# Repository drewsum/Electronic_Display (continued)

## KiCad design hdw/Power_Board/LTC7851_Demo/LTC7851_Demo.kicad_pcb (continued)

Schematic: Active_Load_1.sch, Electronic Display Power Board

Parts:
C1101: 1uF; C_0603; Voltage 16V; Digi-Key PN 1276-6524-1-ND
C1102: 0.1uF; C_0603; Voltage 50V; Digi-Key PN 490-4779-1-ND
C1103: 10uF; CP_Tantalum_Case-B_EIA-3528-21_Reflow; Voltage 16V; Tolerance 10%; Digi-Key PN 399-5034-1-ND
J1101: FG_LOAD; Pin_Header_Straight_1x02_Pitch2.54mm
J1102: ISNS; Pin_Header_Straight_1x02_Pitch2.54mm
Q1101, Q1102: IPC100N04S51R7ATMA1; TDSON-8-1; Digi-Key PN BSC123N10LSGATMA1CT-ND
R1101, R1105, R1106: 10k; R_0603; Tolerance 1%; Digi-Key PN RHM10KADCT-ND
R1102, R1103, R1104: 10; R_0603; Tolerance 1%; Digi-Key PN YAG3351CT-ND
R1107, R1108: 5m; R_2512; Tolerance 1%; Digi-Key PN YAG2145CT-ND
U1101: LT1010DD; DFN-8-1EP_3x3mm_Pitch0.5mm; Digi-Key PN LT1010CDD#PBF-ND

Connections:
+5V: Q1101.5 (D), Q1102.5 (D); also elsewhere on the board
+12V: C1101.1, C1102.1, C1103.1, R1102.1, U1101.1 (V+); also elsewhere on the board
GND: C1101.2, C1102.2, C1103.2, J1101.2, J1102.2, R1101.2, R1105.2, R1106.2, R1107.2, R1108.2, U1101.6 (V-), U1101.9 (V-); also elsewhere on the board
LOAD_GATE: R1103.2, R1104.2, U1101.3; also elsewhere on the board
unnamed: J1101.1, R1101.1, U1101.8
unnamed: J1102.1, Q1101.1 (S), Q1101.2 (S), Q1101.3 (S), R1107.1
unnamed: Q1101.4 (G), R1103.1, R1105.1
unnamed: Q1102.1 (S), Q1102.2 (S), Q1102.3 (S), R1108.1
unnamed: Q1102.4 (G), R1104.1, R1106.1
unnamed: R1102.2, U1101.2 (Bias)

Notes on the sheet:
11. Active Load Driver and Active Load Bank 1

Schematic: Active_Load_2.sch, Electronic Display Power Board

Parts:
Q1201, Q1202: IPC100N04S51R7ATMA1; TDSON-8-1; Digi-Key PN BSC123N10LSGATMA1CT-ND
R1201, R1202: 10; R_0603; Tolerance 1%; Digi-Key PN YAG3351CT-ND
R1203, R1204: 10k; R_0603; Tolerance 1%; Digi-Key PN RHM10KADCT-ND
R1205, R1206: 5m; R_2512; Tolerance 1%; Digi-Key PN YAG2145CT-ND

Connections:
+5V: Q1201.5 (D), Q1202.5 (D); also elsewhere on the board
GND: R1203.2, R1204.2, R1205.2, R1206.2; also elsewhere on the board
LOAD_GATE: R1201.2, R1202.2; also elsewhere on the board
unnamed: Q1201.1 (S), Q1201.2 (S), Q1201.3 (S), R1205.1
unnamed: Q1201.4 (G), R1201.1, R1203.1
unnamed: Q1202.1 (S), Q1202.2 (S), Q1202.3 (S), R1206.1
unnamed: Q1202.4 (G), R1202.1, R1204.1

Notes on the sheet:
12. Active Load Bank 2

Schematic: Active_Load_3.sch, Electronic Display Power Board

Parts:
Q1301, Q1302: IPC100N04S51R7ATMA1; TDSON-8-1; Digi-Key PN BSC123N10LSGATMA1CT-ND
R1301, R1302: 10; R_0603; Tolerance 1%; Digi-Key PN YAG3351CT-ND
R1303, R1304: 10k; R_0603; Tolerance 1%; Digi-Key PN RHM10KADCT-ND
R1305, R1306: 5m; R_2512; Tolerance 1%; Digi-Key PN YAG2145CT-ND

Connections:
+5V: Q1301.5 (D), Q1302.5 (D); also elsewhere on the board
GND: R1303.2, R1304.2, R1305.2, R1306.2; also elsewhere on the board
LOAD_GATE: R1301.2, R1302.2; also elsewhere on the board
unnamed: Q1301.1 (S), Q1301.2 (S), Q1301.3 (S), R1305.1
unnamed: Q1301.4 (G), R1301.1, R1303.1
unnamed: Q1302.1 (S), Q1302.2 (S), Q1302.3 (S), R1306.1
unnamed: Q1302.4 (G), R1302.1, R1304.1

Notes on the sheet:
13. Active Load Bank 3

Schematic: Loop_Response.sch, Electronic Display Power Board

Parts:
J1401: VOUT; Pin_Header_Straight_1x02_Pitch2.54mm
J1402: LOOP_TAP; Pin_Header_Straight_1x02_Pitch2.54mm
J1403: Wave_Gen_In; Pin_Header_Straight_1x02_Pitch2.54mm
T1401: 1:1 Pulse Transformer; Murata_78601_9C; Digi-Key PN 811-2650-ND

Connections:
+5V: J1401.1, T1401.4 (SB); also elsewhere on the board
GND: J1401.2, J1402.2, J1403.2, T1401.2 (AB); also elsewhere on the board
LOOP_TAP: J1402.1, T1401.3 (SA); also elsewhere on the board
unnamed: J1403.1, T1401.1 (AA)

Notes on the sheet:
14. Open Loop Transfer Function Test Components

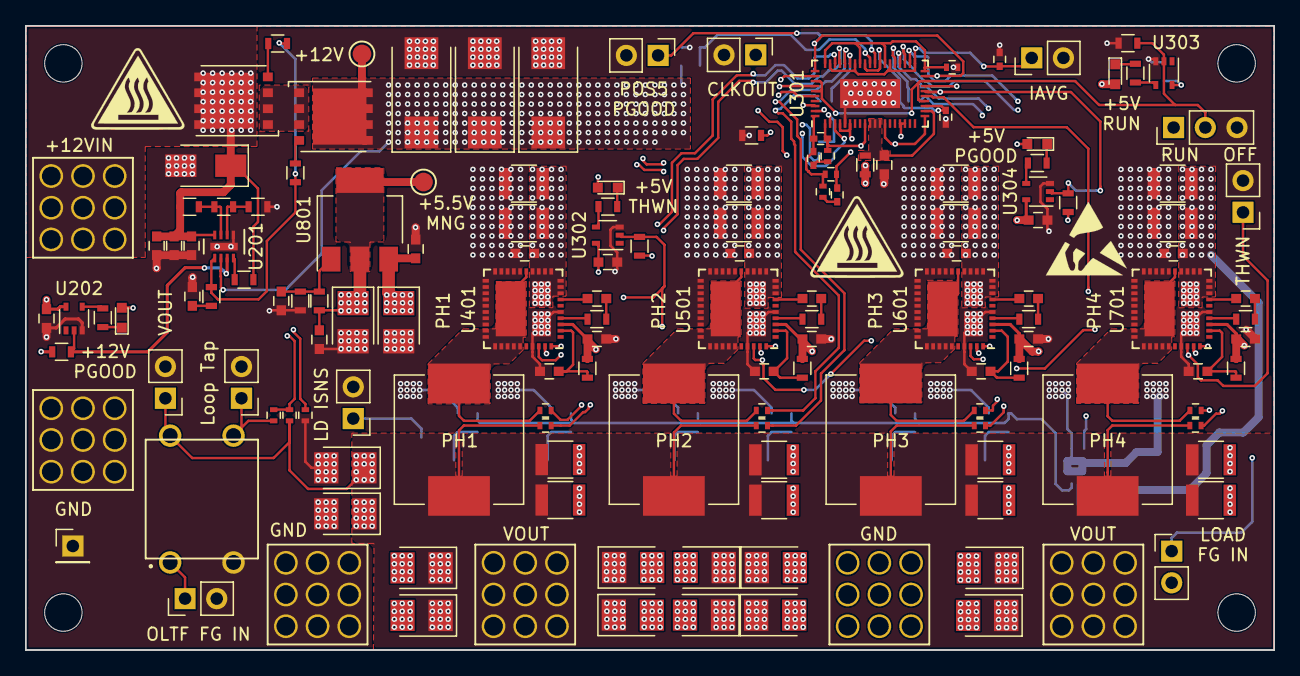
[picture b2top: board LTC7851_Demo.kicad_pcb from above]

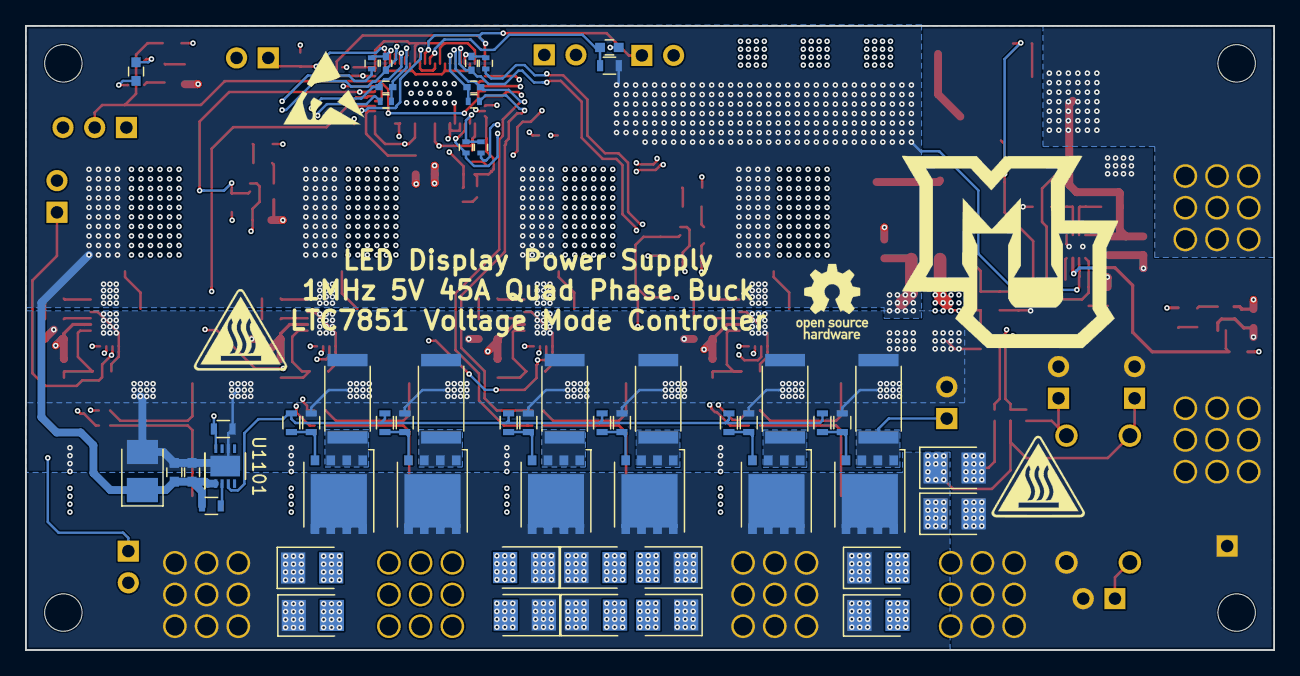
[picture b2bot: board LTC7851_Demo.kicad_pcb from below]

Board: 4 copper layers, 100.0 x 50.0 mm, 208 parts (55 on the bottom side), 94 nets.

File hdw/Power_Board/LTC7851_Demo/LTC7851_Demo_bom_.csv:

References,Value,Quantity Per PCB,Digi-Key PN,display_footprint
C207 C301 C302 C303 C304 C305 C411 C413 C506 C508 C606 C608 C706 C708 C802 C803 C804 C1102,0.1uF,18,490-4779-1-ND,603
C201,0.1uF,1,490-4779-1-ND,603
C415 C510 C610 C710,0.22uF,4,1276-1049-1-ND,402
C401 C402 C406,100pF,3,478-1089-1-ND,402
C204 C206 C208,100uF,3,718-1102-1-ND,7343
C405 C407 C408 C410 C412 C420 C501 C502 C503 C505 C507 C515 C601 C602 C603 C605 C607 C615 C701 C702 C703 C705 C707 C715 C805,100uF,25,478-9994-1-ND,3528
C417 C419 C512 C514 C612 C614 C712 C714,100uF,8,587-3432-1-ND,1210
C202 C205,10nF,2,1276-1921-1-ND,603
C801 C1103,10uF,2,399-5034-1-ND,3528
C203,1nF,1,311-1080-1-ND,603
C409 C414 C509 C604 C609 C704 C709 C1101,1uF,8,1276-6524-1-ND,603
C504,1uF,1,1276-6524-1-ND,603
C404,2200pF,1,478-1105-1-ND,402
C416 C418 C511 C513 C611 C613 C711 C713,22uF,8,445-1436-1-ND,1210
C403,3300pF,1,478-5132-1-ND,402
D201,24V,1,SMAJ24CALFCT-ND,
D202 D302 D303,Green,3,160-1446-1-ND,
D301,Red,1,160-1447-1-ND,
J201,+12V IN,1,732-3214-ND,
J901 J902,+5V OUT,2,732-3214-ND,
J301,CLKOUT,1,,
J1101,FG_LOAD,1,,
J206,GND IN,1,732-3214-ND,
J903 J904,GND OUT,2,732-3214-ND,
J304,IAVG,1,,
J1102,ISNS,1,,
J1402,LOOP_TAP,1,,
J305,PGOOD,1,,
J302,RUN,1,,
J303,THDN,1,,
J1401,VOUT,1,,
J1403,Wave_Gen_In,1,,
L401 L501 L601 L701,0.47uH,4,541-2595-1-ND,IHLP4040
MK1001 MK1002 MK1009 MK1010,4-40 Screw,4,36-9900-ND,
MK1003 MK1004 MK1011 MK1012,4-40 Standoff,4,36-8400-ND,
Q201 Q202 Q1101 Q1102 Q1201 Q1202 Q1301 Q1302,IPC100N04S51R7ATMA1,8,BSC123N10LSGATMA1CT-ND,
R301,0,1,311-0.0GRCT-ND,603
R408 R412 R413 R414 R504 R505 R604 R605 R704 R705,0,10,RMCF0402ZT0R00CT-ND,402
R407 R503 R603 R703,1.4k,4,RMCF0402FT1K40CT-ND,402
R205 R206 R1102 R1103 R1104 R1201 R1202 R1301 R1302,10,9,YAG3351CT-ND,603
R409,10,1,311-10.0LRCT-ND,402
R204,100k,1,P100KHCT-ND,603
R410,100k,1,311-100KLRCT-ND,402
R207 R304 R305 R310 R1101 R1105 R1106 R1203 R1204 R1303 R1304,10k,11,RHM10KADCT-ND,603
R404,10k,1,311-10.0KLRCT-ND,402
R411,13.7k,1,311-13.7KLRCT-ND,402
R209 R306 R307 R308,1k,4,RHM1.0KDCT-ND,603
R302 R405 R406 R501 R502 R601 R602 R701 R702,2,9,RMCF0603FT2R00CT-ND,603
R801,200,1,MCT0603-200-CFCT-ND,603
R203,243k,1,541-243KHCT-ND,603
R402,324,1,YAG3118CT-ND,402
R208,5.1k,1,RMCF0603FT5K10CT-ND,603
R303,51.1k,1,P51.1KHCT-ND,603
R1107 R1108 R1205 R1206 R1305 R1306,5m,6,YAG2145CT-ND,2512
R201,6.04M,1,541-6.04MHCT-ND,603
R403,6.04k,1,RMCF0402FT6K04CT-ND,402
R401,66.5k,1,RMCF0402FT66K5CT-ND,402
R802,680,1,P680HCT-ND,603
R202,86.6k,1,311-86.6KHRCT-ND,603
T1401,1:1 Pulse Transformer,1,811-2650-ND,
U202 U303 U304,74LVC1G06,3,296-8484-1-ND,
U302,74LVC1G17,1,296-11934-1-ND,
U801,LM1117-ADJ,1,LM1117IMPX-ADJ/NOPBCT-ND,
U1101,LT1010DD,1,LT1010CDD#PBF-ND,
U201,LTC4365DDB,1,LTC4365IDDB#TRMPBFCT-ND,
U301,LTC7851UHH,1,LTC7851IUHH#PBF-ND,
U401 U501 U601 U701,SiC779,4,SIC779CD-T1-GE3CT-ND,

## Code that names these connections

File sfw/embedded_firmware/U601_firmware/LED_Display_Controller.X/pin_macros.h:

/* ************************************************************************** */
/** Descriptive File Name

  @Company
    Company Name

  @File Name
    filename.h

  @Summary
    Brief description of the file.

  @Description
    Describe the purpose of this file.
 */
/* ************************************************************************** */

#ifndef _PIN_MACROS_H    /* Guard against multiple inclusion */
#define _PIN_MACROS_H

#include <xc.h>

// These pin macros allow for easier manipulation of GPIO with matching
// signal names from the hardware schematic

// PORTA Pin Macros
#define nLEVEL_SHIFT_EN_PIN         LATAbits.LATA0
#define nFLASH_WP7_PIN              LATAbits.LATA2
#define nFLASH_WP8_PIN              LATAbits.LATA3
#define nFLASH_WP1_PIN              LATAbits.LATA6
#define nFLASH_WP2_PIN              LATAbits.LATA7
#define nFLASH_WP3_PIN              LATAbits.LATA9
#define nFLASH_WP4_PIN              LATAbits.LATA10
#define nFLASH_WP5_PIN              LATAbits.LATA14
#define nFLASH_WP6_PIN              LATAbits.LATA15

// PORTB Pin Macros
#define nFLASH_CE1_PIN              LATBbits.LATB2
#define nFLASH_CE2_PIN              LATBbits.LATB3
#define nFLASH_CE3_PIN              LATBbits.LATB4
#define nFLASH_CE4_PIN              LATBbits.LATB5
#define nFLASH_CE5_PIN              LATBbits.LATB6
#define nFLASH_CE6_PIN              LATBbits.LATB7
#define nFLASH_CE7_PIN              LATBbits.LATB10
#define nFLASH_CE8_PIN              LATBbits.LATB11
#define nFLASH_HOLD_PIN             LATBbits.LATB12
#define FLASH_SCK_PIN               LATBbits.LATB14

// PORTC Pin Macros
#define FLASH_MOSI_PIN              LATCbits.LATC13
#define FLASH_MISO_PIN              PORTCbits.RC14

// PORTE Pin Macros
#define WIFI_CHPD_PIN               LATEbits.LATE8
#define nWIFI_RESET_PIN             LATEbits.LATE9

// PORTF Pin Macros
#define POS12_PGOOD_PIN             PORTfbits.RF1
#define POS5_RUN_PIN                LATFbits.LATF2
#define POS5_PGOOD_PIN              PORTFbits.RF3
#define POS5P_PGOOD_PIN             PORTFbits.RF8
#define nPOS5P_THWN_PIN             PORTFbits.RF12
#define POS5P_RUN_PIN               LATFbits.LATF13

// PortG Pin Macros
#define PANEL_DIM_PWM_PIN           LATGbits.LATG0
#define EBI_ERROR_LED_PIN           LATGbits.LATG1
#define SPI_ERROR_LED_PIN           LATGbits.LATG6
#define HEARTBEAT_LED_PIN           LATGbits.LATG12
#define WIFI_ERROR_LED_PIN          LATGbits.LATG13
#define USB_ERROR_LED_PIN           LATGbits.LATG14
#define nACTIVE_LED_PIN             LATGbits.LATG15

// Port H Pin Macros
#define OTHER_ERROR_LED_PIN         LATHbits.LATH3

// Port J Pin Macros
#define PANEL_CLK_PIN               LATJbits.LATJ0
#define PANEL_LAT_PIN               LATJbits.LATJ1
#define nPANEL_OE_PIN               LATJbits.LATJ2

// Port K Pin Macros
#define nDISPLAY_ENABLE_PIN         PORTKbits.RK4
#define ENCODER_STEP_PIN            PORTKbits.RK5
#define ENCODER_DIR_PIN             PORTKbits.RK6
#define POS3P3_PGOOD_PIN            PORTKbits.RK7

#endif /* _PIN_MACROS_H */

/* *****************************************************************************
 End of File
 */

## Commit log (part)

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2018-11-07 Added encoder stuff
2018-11-08 Merged USB UART functionality into four by four panel test project
2018-11-08 Added blinking heartbeat LED functionality
2018-11-12 revised part numbers in BOM
2018-11-12 Added power board monitoring circuits
2018-11-14 Fixed row select and flickering issues
2018-11-14 Added a to do list entry
2018-11-16 Added a few pages and edits
2018-11-16 Added panel output enable AND gate
2018-11-16 merging Log's changes on micro sheets
2018-11-16 forced merge pull request to override master
2018-11-16 I said never do this, it's bad for you
2018-11-16 Wired a lot of signals to micro, added COM port notes
2018-11-16 Added graphical symbols to certain sheets
2018-11-17 Added aux +12V barrel jack
2018-11-20 Added item to to do list
2018-11-20 bug fixes for correct color
2018-11-21 Added changes to power board BOM
2018-11-21 Reordered sheets in table of contents
2018-11-21 Renamed some sheets and added sheet titles to table of contents
2018-11-22 Added titles and MU logo to each sheet
2018-11-26 Added acrylic cutouts SVG
2018-11-26 rage commit
2018-11-28 Added a few notes to power board schematic
2018-11-28 Schematic cleanup
2018-11-28 Edited sheet block company field
2018-12-01 partial 4x4 support
2018-12-01 added features such as set rgb stripes, christmas stripes, red rows(doesn't work)
2018-12-02 Added a bunch of test images
2018-12-02 fixing screen switching code and image contrast
2018-12-02 Added slowest mux speed command
2018-12-03 Added to do list items
2018-12-03 Changed a few pull resistors
2018-12-03 Finished SRAM custom footprint
2018-12-04 Added other error LED
2018-12-04 added ESP8266 custom footprint
2018-12-06 Added some digikey partnumbers to components
2018-12-06 First pass assignment of footprints to all components
2018-12-06 Generated first preliminary netlist
2018-12-06 Updated sch PDF after prelim netlist generation
2018-12-06 Added first pass BOM
2018-12-06 Modified BOM
2018-12-07 Redesigned POS3P3 supply with new controller for 5 amps
2018-12-09 Placed decoupling caps around micro
2018-12-09 Placed SRAM
2018-12-09 arranged rotary encoder parts
2018-12-11 Added documentation/datasheets for parts
2018-12-11 Arranged power supply parts
2018-12-12 Arranged USB, routed EBI
2018-12-13 Placed ADC filter parts
2018-12-13 Resolved pinout issue with TVS diodes
2018-12-13 Placed parts for WIFI module
2018-12-13 Fixed FLASH reference designators
2018-12-14 Fixed reference designators for level shifting/flash copies
2018-12-14 Added custom IDC connector footprint
2018-12-14 Corrected output data TVS diodes
2018-12-14 Fixed ESD protection on data connectors again
2018-12-15 First pass of placing parts
2018-12-15 Placed more parts, added some labels
2018-12-16 Added flash chip select LEDs
2018-12-16 Added WIFI comm LED
2018-12-16 Added additional capacitance sheet
2018-12-16 Added layer count
2018-12-16 Added a lot more status LEDs
2018-12-16 Placed more new parts
2018-12-18 Resolved panel data connector orientation issues
2018-12-19 Added bare metal test program
2018-12-19 commit so ren can pull
2018-12-19 Routed a bunch of traces
2018-12-20 Routed a lot
2018-12-20 More rowts
2018-12-20 Added manufacturer logos
2018-12-20 Added menufacturer logos
2018-12-20 Added embedded firmware project
2018-12-20 new bom
2018-12-20 Routed panel control signals
2018-12-20 created gpio_setup.h and gpio_setup.c
2018-12-21 adding some macros, thru portF
2018-12-21 More routing, what else is new
2018-12-24 Made a few more critical routes
2018-12-24 Routed a few more traces
2018-12-24 Trying to cleanly merge two firmware branches
2018-12-24 More routing
2018-12-24 Succefully merged carolware and logware into drewware
2018-12-27 Added some interrupt control APIs
2018-12-27 Added global interrupt manipulation functions
2018-12-27 Added functions to read interrupt flags and enables
2019-01-02 Added priority interrupt functions, hearbeat to bare metal example
2019-01-03 Removed old files from firmware project
2019-01-05 More routing, added POS12 PGOOD net to micro
2019-01-05 Finished writing pin macros
2019-01-05 Added error handler header file
2019-01-08 Added cause of reset files, nothing filled in yet
2019-01-08 Added power saving files
2019-01-08 Added a bunch of blank headers/source files for future programming
2019-01-08 Reordered inclusions in main
2019-01-08 Removed duplicate hdw folder, added watchdog sfw file
2019-01-08 Wrote WDT functions
2019-01-08 Filled in peripheral map a little more
2019-01-08 Added in DMT functions intp hearbeat ISR, startup, etc
2019-01-10 Added stitching caps, mor erouting
2019-01-10 Added PMD and PPS lock/unlock functions
2019-01-11 Added trick marquette copper logos
2019-01-11 Added bigger QR code, LTC logo
2019-01-11 Added some cool imageS
2019-01-11 add in app icon and database
2019-01-11 Added MU seal
2019-01-14 Cleaned up a few tracks
2019-01-14 More cleaning
2019-01-18 Added USB UART functions
2019-01-28 Started programming board
2019-01-29 Got WDT working
2019-01-29 Got DMT working
2019-01-29 Added initial testing scope captures
2019-01-29 Added UART scope captures
2019-01-29 Got USB UART receiving working, sorta
2019-01-29 Added some serial commands
2019-01-30 Resolved merge conflicts, added a lot of functionality
2019-01-31 Wrote cause of Reset code
2019-01-31 Added reset debug data to boot debug message
2019-01-31 Removed RCON bit clearing in cause of reset function
2019-01-31 Changed all status debug messages to printf statements
2019-01-31 Added interrupt debug commands
2019-01-31 Tried to fix POS5 run situation, did not work
2019-01-31 Added RF2 PPS setting
2019-02-01 Configured all GPIO digital output PPS settings
2019-02-01 Added serial commands to print device ID information
2019-02-01 Edited some debug strings
2019-02-01 started EBI
2019-02-01 Removed Room DB, replaced with TinyDB
2019-02-02 Added SBV interrupt, error handling, trying to fix more USB issues with long messages
2019-02-02 Set theme jekyll-theme-minimal
2019-02-03 Added basic exception handling code without recovery
2019-02-03 Added core timer functions and ISR
2019-02-03 Resolved USB UART ring buffer exception issue
2019-02-04 Added clock status serial message
2019-02-04 Altered PMD status message to change color based on status
2019-02-04 Added conditional text coloring to a few print funtions
2019-02-04 Added error handling stuff an resolved multi-vector int issue
2019-02-04 Added alternate config word settings
2019-02-05 Added prefetch code
2019-02-05 SPI flash firmware and added status message to usb_uart.c
2019-02-05 fix build failures
2019-02-05 added EditProjectFragment and redeveloped NewProjectFragment
2019-02-05 Edited gitignore for netbeans projects
2019-02-05 Removed netbeans project settings from repo
2019-02-05 qlkjwehrlkqjwner
2019-02-05 more ignoring
2019-02-06 Added functions for writing, reading, and testing EBI
2019-02-06 changed what we're ignoring
2019-02-07 Added ADC init code, not working yet
2019-02-07 Got basic ADC init function working
2019-02-07 ignoreeeeeee
2019-02-07 ignore ignore ignore
2019-02-07 Got basic ADC driver working
2019-02-08 Added ISRs for copying data for used ADC channel
2019-02-08 Added serial commands/ISRs to measure board voltages
2019-02-08 Added a bunch of ADC code
2019-02-08 Added stuff to ADC status serial command
2019-02-08 Edited interrupt status function
2019-02-10 Added a bunch of code for EBI
2019-02-10 Removed dumb _config.yml file for a github feature we're not using
2019-02-10 Trying to solve EBI SRAM issues
2019-02-11 preliminary panel control stuff
2019-02-12 test buffer fills, panel control
2019-02-12 Drew's on carol's branch
2019-02-12 fixed converter, started passing vars between screens
2019-02-12 add delete project
2019-02-12 Cleaned up serial commands and other stuff
2019-02-20 fix selection issue, generalized some classes
2019-02-22 ADC enhancements
2019-02-22 Added a few ADC messages to serial commands
2019-02-22 More bug fixes
2019-02-23 optimization and some spi stuff
2019-02-26 preview Images, update ren's FileConverter code
2019-02-26 PPT update
2019-02-26 Some optimizations
2019-02-27 Added internal RAM buffer and split from EBI SRAM
2019-02-27 Removed enhanced buffer mode from SPI Flash driver
2019-02-27 Added more SPI Flash error recording
2019-02-27 First pass at reusing USB_UART code
2019-03-01 Added PWM function prototypes
2019-03-01 string handling
2019-03-02 dimming on OC3
2019-03-02 Speed optimizations in multiplexing handler
2019-03-02 Trying more speed optimizations in muxing handler
2019-03-05 Even more speed optimizations
2019-03-05 Added second test image
2019-03-06 created an "image row" to view thumbnails, switch to 5 bit color
2019-03-06 Config error bug fixes/adjustments
2019-03-07 Made device_on_time a persistent variabel
2019-03-08 Edited prefetch settings, removed core timer ISR
2019-03-08 saving off changes to switch branches = boring
2019-03-08 WE ARE BACK!
2019-03-08 lets see what happens
2019-03-08 Trying to get SPI Flash to work
2019-03-15 Few SPI Flash fixes, not there yet
2019-03-15 More SPI Flash work
2019-03-15 Think I got SPI Flash Writing working
2019-03-15 Some boot clock setting changes
2019-03-15 Added SVG file for logic board gaurd
2019-03-18 images change order
2019-03-18 changes... meh
2019-03-20 allow android libs to reduce sdk size
2019-03-22 Got basic WIFI UART driver working
2019-03-22 fixed vectors that were not displaying
2019-03-22 debuging esp uart
2019-03-24 debugging esp rx/tx and added Timer4 as delay timer
2019-03-24 AT commands work
2019-03-25 start debugging WiFi
2019-03-25 added device control functionality
2019-03-25 test111
2019-03-25 PPT screen shot Bitmap
2019-03-25 abstracted WiFi code over to WiFi controller
2019-03-26 finished change notification stuff, hope it works
2019-03-26 some wifi debugging
2019-03-26 Added a ton of WIFI UART stuff
2019-03-26 having git issues part 2
2019-03-27 fixed problems with changing image order
2019-03-27 fix keyboard shrinking layout
2019-03-29 Got dimming PWM working
2019-03-29 Fixed PWM frequency issue
2019-03-29 test sending bytes
2019-03-29 Fixed IO Change notifications
2019-03-30 Change notification cleanups
2019-03-30 Edited peripheral spreadsheet
2019-03-31 SPI Flash data check
2019-03-31 More speed optimizations
2019-04-01 switch to TCP from HTTP, bug in deleting devices, debugging wifi
2019-04-01 some cleanup
2019-04-01 more clean up
2019-04-02 updated gradle version
2019-04-02 Added system control from ESP
2019-04-02 fix casting and string literals
2019-04-04 Few SPI timing changes
2019-04-04 Trying to parse image data
2019-04-05 Got image transfer working
2019-04-07 text update bug, sending full image
2019-04-07 More wifi additions
2019-04-07 dark background on splash
2019-04-08 Got frame count NVM variable working
2019-04-08 Few wifi changes
2019-04-08 More wifi fixes
2019-04-08 state machine werks
2019-04-08 sending multiple kind of works
2019-04-09 Sends all 8 images
2019-04-09 fixed state machine
2019-04-10 state machine additions
2019-04-10 Added ignored file to gitignore
2019-04-10 Few bug fixes
2019-04-13 many tiny fixes, started progress bar, fixed preview, dim bar, header titles
2019-04-13 variable time delay, rotating images, change project storage
2019-04-14 Hard master merge from drewbrach_diverge
2019-04-14 Updated Readme to include software versions
2019-04-15 fix storage bugs, new placeholder images
2019-04-18 Added a few firmware tweaks
2019-04-18 fixed backstack overlaying, removed splash screen, added back button to image select
2019-04-18 data manager changes
2019-04-18 Added tweaks to project values serial command
2019-04-18 fixed project preview issues, added some wifi code to auto-connect
2019-04-23 fix app title, remove AT command support, add about page content
2019-04-24 starting the linting
2019-04-24 more linting
2019-04-24 Removed unneeded files
2019-04-26 final touches for progress bar
2019-04-26 Added ESP timeout support
2019-04-26 Added image transitions
2019-04-27 Fixed SPI Flash bug when reading first image in state machine
2019-04-29 screen "on" during upload, only portrait mode
2019-04-29 Added Cris READMEs
2019-04-29 screen rotation not allowed
2019-04-30 started to remove strings
2019-04-30 string resources, init checks, switch statements
2019-04-30 Rebrand frames to slides
2019-05-01 fix spacing
2019-05-03 new version for play store
2019-05-05 Regenerated hdw pdfs
